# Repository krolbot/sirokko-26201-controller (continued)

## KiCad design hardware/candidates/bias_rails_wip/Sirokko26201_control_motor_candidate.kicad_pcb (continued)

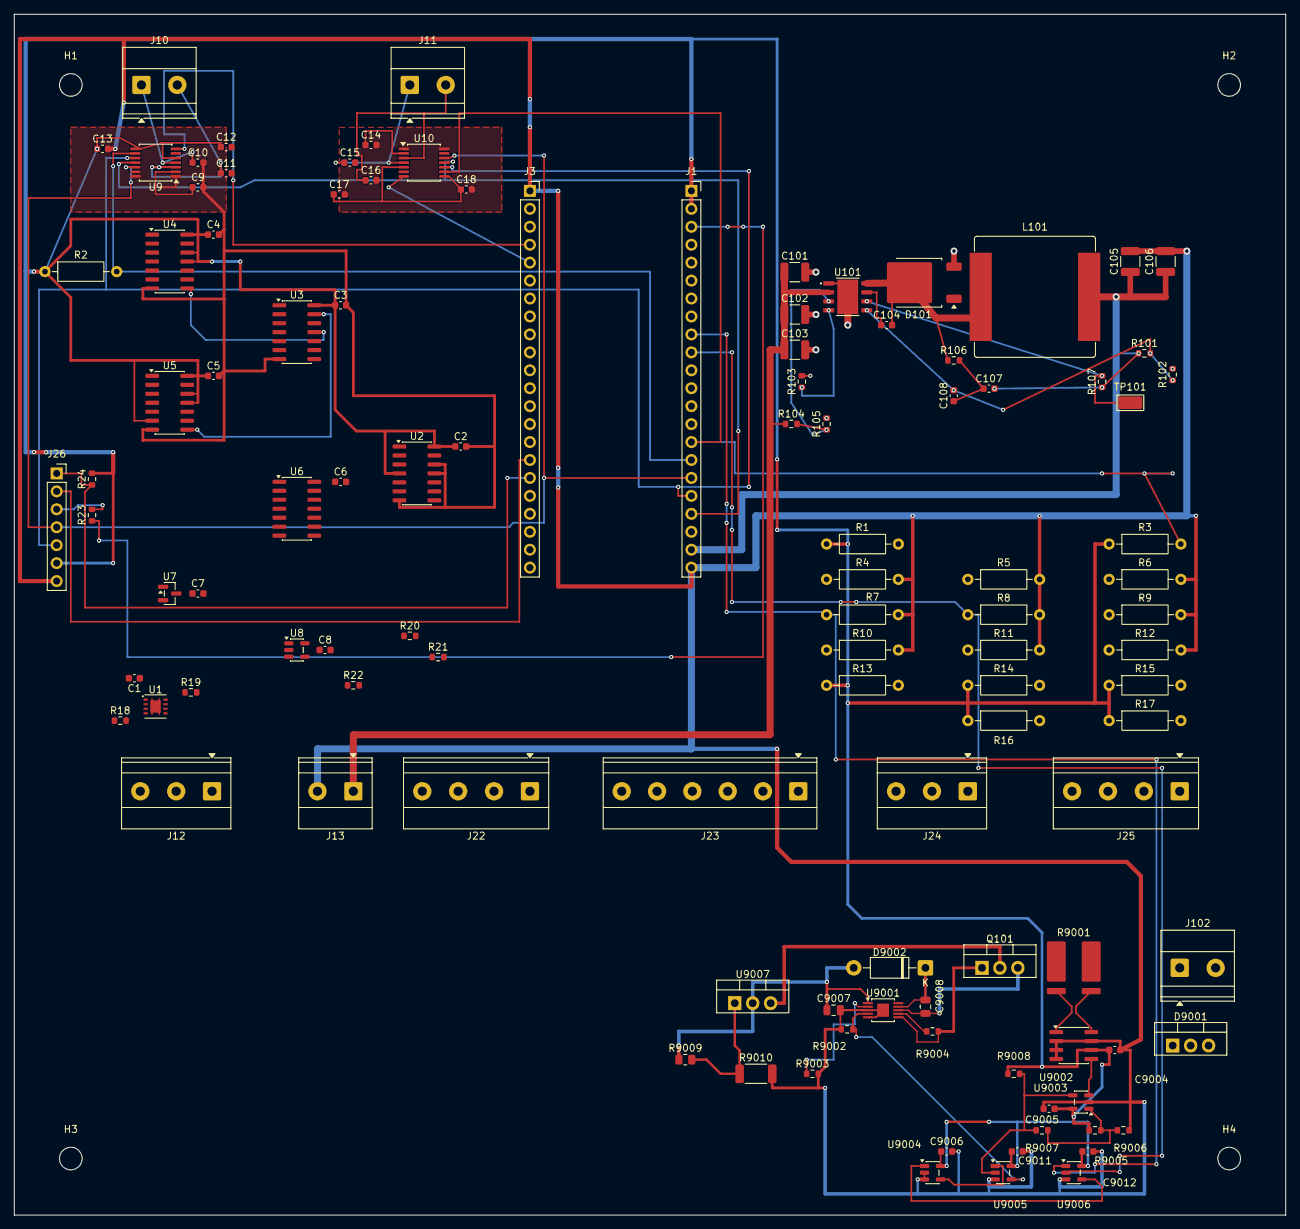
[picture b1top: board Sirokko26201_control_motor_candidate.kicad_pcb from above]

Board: 2 copper layers, 180.0 x 170.0 mm, 114 parts (0 on the bottom side), 75 nets.

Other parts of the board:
C9011: 100nF X7R 16V 10%; U9005 local bypass; C_0603_1608Metric
C9012: 100nF X7R 16V 10%; U9006 local bypass; C_0603_1608Metric
H1, H2, H3, H4: M3; MountingHole_3.2mm_M3

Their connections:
/+3V3: C9011.1, C9012.1; also elsewhere on the board
/GND: C9011.2, C9012.2; also elsewhere on the board

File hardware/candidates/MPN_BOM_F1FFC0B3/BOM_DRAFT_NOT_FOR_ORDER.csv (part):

"Ref","Value","Footprint","Qty","DNP","MPN","Manufacturer","Datasheet"
"C1","100n 16V X7R","Capacitor_SMD:C_0603_1608Metric","1","","","",""
"C2","100n 16V X7R","Capacitor_SMD:C_0603_1608Metric","1","","","",""
"C3","100n 16V X7R","Capacitor_SMD:C_0603_1608Metric","1","","","",""
"C4","100n 16V X7R","Capacitor_SMD:C_0603_1608Metric","1","","","",""
"C5","100n 16V X7R","Capacitor_SMD:C_0603_1608Metric","1","","","",""
"C6","100n 16V X7R","Capacitor_SMD:C_0603_1608Metric","1","","","",""
"C7","100n 16V X7R","Capacitor_SMD:C_0603_1608Metric","1","","","",""
"C8","100n 16V X7R","Capacitor_SMD:C_0603_1608Metric","1","","","",""
"C9","0.1uF X7R 16V BIAS","Capacitor_SMD:C_0603_1608Metric","1","","","",""
"C10","0.01uF X7R 16V T+ filter","Capacitor_SMD:C_0603_1608Metric","1","","","",""
"C11","0.01uF X7R 16V T- filter","Capacitor_SMD:C_0603_1608Metric","1","","","",""
"C12","0.1uF X7R 16V AVDD","Capacitor_SMD:C_0603_1608Metric","1","","","",""
"C13","0.1uF X7R 16V DVDD","Capacitor_SMD:C_0603_1608Metric","1","","","",""
"C14","0.1uF X7R 16V BIAS","Capacitor_SMD:C_0603_1608Metric","1","","","",""
"C15","0.01uF X7R 16V T+ filter","Capacitor_SMD:C_0603_1608Metric","1","","","",""
"C16","0.01uF X7R 16V T- filter","Capacitor_SMD:C_0603_1608Metric","1","","","",""
"C17","0.1uF X7R 16V AVDD","Capacitor_SMD:C_0603_1608Metric","1","","","",""
"C18","0.1uF X7R 16V DVDD","Capacitor_SMD:C_0603_1608Metric","1","","","",""
"C19","10n ENC_A_FILTER","Capacitor_SMD:C_0603_1608Metric_Pad1.08x0.95mm_HandSolder","1","","","",""
"C20","10n ENC_B_FILTER","Capacitor_SMD:C_0603_1608Metric_Pad1.08x0.95mm_HandSolder","1","","","",""
"C75","10n","Capacitor_SMD:C_0603_1608Metric_Pad1.08x0.95mm_HandSolder","1","","","",""
"C101","2.2uF 100V X7R","Capacitor_SMD:C_1210_3225Metric","1","","GRM32ER72A225KA35L","",""
"C102","2.2uF 100V X7R","Capacitor_SMD:C_1210_3225Metric","1","","GRM32ER72A225KA35L","",""
"C103","22uF 100V BULK","Capacitor_SMD:C_1210_3225Metric","1","","GRM32ER72A226KE20L","",""
"C104","2.2nF 50V X7R","Capacitor_SMD:C_0603_1608Metric","1","","CC0603KRX7R9BB222","",""
"C105","47uF 16V X7R","Capacitor_SMD:C_1210_3225Metric","1","","GRM32ER61C476KE15L","",""
"C106","47uF 16V X7R","Capacitor_SMD:C_1210_3225Metric","1","","GRM32ER61C476KE15L","",""
"C107","4.7nF 50V C0G","Capacitor_SMD:C_0603_1608Metric","1","","GRM1885C1H472JA01D","",""
"C108","820pF 50V C0G","Capacitor_SMD:C_0603_1608Metric","1","","CC0603JRNPO9BN821","",""
"C301","10uF GRM21BR61E106KA73L","Sirokko_TFT_Passives:C_Murata_GRM21B_2012_Reflow","1","","","",""
"C302","10uF GRM21BR61E106KA73L","Sirokko_TFT_Passives:C_Murata_GRM21B_2012_Reflow","1","","","",""
"C303","100nF GRM188R71E104KA01D","Sirokko_TFT_Passives:C_Murata_GRM188_1608_Reflow","1","","","",""
"C304","47uF GRM32ER61C476KE15L","Sirokko_TFT_Passives:C_Murata_GRM32E_3225_Reflow","1","","","",""
"C305","100nF","Capacitor_SMD:C_0603_1608Metric","1","","","",""
"C306","100nF","Capacitor_SMD:C_0603_1608Metric","1","","","",""
"C9004","100nF X7R 16V","Capacitor_SMD:C_0603_1608Metric","1","","","",""
"C9005","100nF X7R 16V","Capacitor_SMD:C_0603_1608Metric","1","","","",""
"C9006","100nF X7R 16V","Capacitor_SMD:C_0603_1608Metric","1","","","",""
"C9007","1uF ±10% X7R 50V 0805; LTC7001 VCC local decoupling","Capacitor_SMD:C_0805_2012Metric","1","","GRM21BR71H105KA12L","",""
"C9008","1uF ±10% X7R 50V 0805 (BST-TS)","Capacitor_SMD:C_0805_2012Metric","1","","GRM21BR71H105KA12L","",""
"C9011","100nF X7R 16V 10%; U9005 local bypass","Capacitor_SMD:C_0603_1608Metric","1","","","",""
"C9012","100nF X7R 16V 10%; U9006 local bypass","Capacitor_SMD:C_0603_1608Metric","1","","","",""
"D101","STPS5H100B-TR","","1","","STPS5H100B-TR","",""
"D9001","STPS30H100CW; common cathode: K/pin2/tab -> MOTOR_POS; A1/pin1 + A2/pin3 -> GND","Package_TO_SOT_THT:TO-220-3_Vertical","1","","STPS30H100CW","","https://www.st.com/resource/en/datasheet/stps30h100c.pdf"
"D9002","MMBD1501A; 200V 200mA silicon low-leakage bootstrap diode","Package_TO_SOT_SMD:SOT-23","1","","MMBD1501A","ON Semiconductor / Fairchild",""
"J1","DEVKITC1_J1","Connector_PinSocket_2.54mm:PinSocket_1x22_P2.54mm_Vertical","1","","","",""
"J3","DEVKITC1_J3","Connector_PinSocket_2.54mm:PinSocket_1x22_P2.54mm_Vertical","1","","","",""
"J10","TC_K_EXHAUST_T+_T-","TerminalBlock_Phoenix:TerminalBlock_Phoenix_MKDS-1,5-2-5.08_1x02_P5.08mm_Horizontal","1","","","",""
"J11","TC_K_AIR_T+_T-","TerminalBlock_Phoenix:TerminalBlock_Phoenix_MKDS-1,5-2-5.08_1x02_P5.08mm_Horizontal","1","","","",""
"J12","ROOM_DS18B20_HARNESS","TerminalBlock_Phoenix:TerminalBlock_Phoenix_MKDS-1,5-3-5.08_1x03_P5.08mm_Horizontal","1","","1715734","Phoenix Contact","https://static.chipdip.ru/lib/723/DOC011723280.pdf"
"J13","24V_LOGIC_INPUT_ONLY__DRAFT_NOT_FOR_ORDER","TerminalBlock_Phoenix:TerminalBlock_Phoenix_MKDS-1,5-2-5.08_1x02_P5.08mm_Horizontal","1","","1715721","Phoenix Contact","https://static.chipdip.ru/lib/509/DOC040509545.pdf"
"J22","START_STOP B3F-4055 + B32-1380 RED","Button_Switch_THT:SW_SPST_Omron_B3F-40xx","1","","","",""
"J23","ENCODER EC11E15244G1","Sirokko_Panel:RotaryEncoder_Alps_EC11E15244G1","1","","","",""
"J24","RESET NKK BB25AB-FA","Sirokko_Panel:SW_NKK_BB25AB-FA","1","","","",""
"J25","THERMAL_AND_HW_ENABLE_3V3_ONLY","TerminalBlock_Phoenix:TerminalBlock_Phoenix_MKDS-1,5-4-5.08_1x04_P5.08mm_Horizontal","1","","","",""
"J26","TFT_WAVESHARE_18366_CABLE_8P","Sirokko_Connectors:Connfly_DS1021_1x08_P2.54mm_Type1_Drill1.02","1","","DS1021-1*8SF11-B","Connfly",""
"J27","GLOW_OUTPUT_PHOENIX_1756993__POWER_PATH_NOT_CONNECTED","Sirokko_Power:Phoenix_1756993_MKDS5HV_2_9.52_ZSZS","1","","1756993","",""
"J28","CLUTCH_OUTPUT_PHOENIX_1756993__POWER_PATH_NOT_CONNECTED","Sirokko_Power:Phoenix_1756993_MKDS5HV_2_9.52_ZSZS","1","","1756993","",""
"J102","MOTOR_24V_HIGH_SPEED; 125W_HEATER_NAMEPLATE_NOT_MOTOR_RATING","TerminalBlock_Phoenix:TerminalBlock_Phoenix_MKDS-1,5-2-5.08_1x02_P5.08mm_Horizontal","1","","","",""
"L101","33uH Isat>=10A","Inductor_SMD:L_Bourns_SRP1770TA_16.9x16.9mm","1","","SRP1770TA-330M","",""
"L301","744025003 3.3uH","Sirokko_TFT_Passives:L_Wuerth_744025003_2828_Reflow","1","","","",""
"Q101","IRFB4110PBF (100V; RDS(on) @ VGS=10V)","Package_TO_SOT_THT:TO-220-3_Vertical","1","","","",""
"R1","4k7","Resistor_THT:R_Axial_DIN0207_L6.3mm_D2.5mm_P10.16mm_Horizontal","1","","","",""
"R2","10k","Resistor_THT:R_Axial_DIN0207_L6.3mm_D2.5mm_P10.16mm_Horizontal","1","","","",""
"R3","10k","Resistor_THT:R_Axial_DIN0207_L6.3mm_D2.5mm_P10.16mm_Horizontal","1","","","",""
"R4","10k","Resistor_THT:R_Axial_DIN0207_L6.3mm_D2.5mm_P10.16mm_Horizontal","1","","","",""
"R5","10k","Resistor_THT:R_Axial_DIN0207_L6.3mm_D2.5mm_P10.16mm_Horizontal","1","","","",""
"R6","10k","Resistor_THT:R_Axial_DIN0207_L6.3mm_D2.5mm_P10.16mm_Horizontal","1","","","",""
"R7","10k","Resistor_THT:R_Axial_DIN0207_L6.3mm_D2.5mm_P10.16mm_Horizontal","1","","","",""
"R8","10k","Resistor_THT:R_Axial_DIN0207_L6.3mm_D2.5mm_P10.16mm_Horizontal","1","","","",""
"R9","10k","Resistor_THT:R_Axial_DIN0207_L6.3mm_D2.5mm_P10.16mm_Horizontal","1","","","",""
"R10","10k","Resistor_THT:R_Axial_DIN0207_L6.3mm_D2.5mm_P10.16mm_Horizontal","1","","","",""
"R11","10k","Resistor_THT:R_Axial_DIN0207_L6.3mm_D2.5mm_P10.16mm_Horizontal","1","","","",""
"R12","10k","Resistor_THT:R_Axial_DIN0207_L6.3mm_D2.5mm_P10.16mm_Horizontal","1","","","",""
"R13","10k","Resistor_THT:R_Axial_DIN0207_L6.3mm_D2.5mm_P10.16mm_Horizontal","1","","","",""
"R14","10k","Resistor_THT:R_Axial_DIN0207_L6.3mm_D2.5mm_P10.16mm_Horizontal","1","","","",""
"R15","10k","Resistor_THT:R_Axial_DIN0207_L6.3mm_D2.5mm_P10.16mm_Horizontal","1","","","",""
"R16","2.2k ENC_A_PULLUP","Resistor_THT:R_Axial_DIN0207_L6.3mm_D2.5mm_P10.16mm_Horizontal","1","","","",""
"R17","2.2k ENC_B_PULLUP","Resistor_THT:R_Axial_DIN0207_L6.3mm_D2.5mm_P10.16mm_Horizontal","1","","","",""
"R18","10k 1%","Resistor_SMD:R_0603_1608Metric","1","","","",""
"R19","10k 1%","Resistor_SMD:R_0603_1608Metric","1","","","",""
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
